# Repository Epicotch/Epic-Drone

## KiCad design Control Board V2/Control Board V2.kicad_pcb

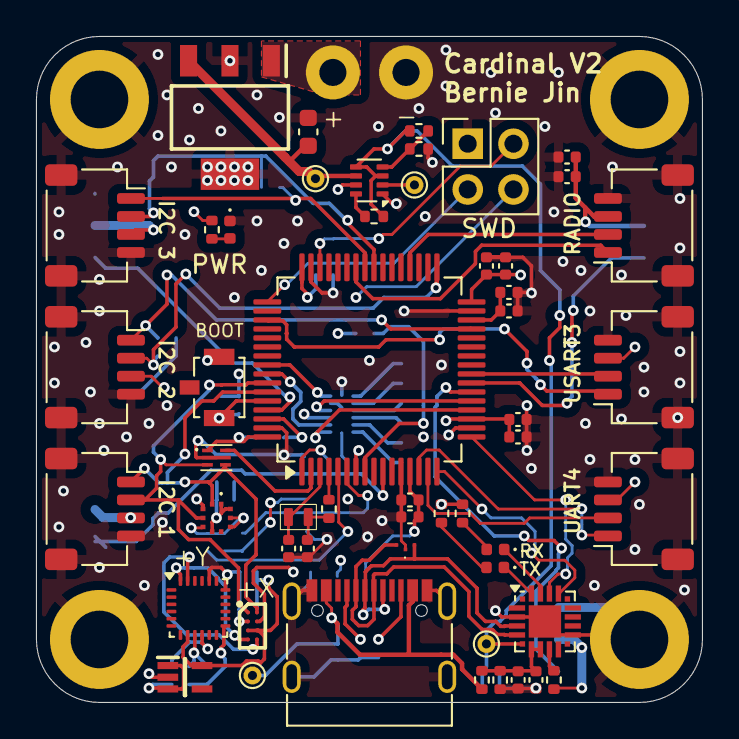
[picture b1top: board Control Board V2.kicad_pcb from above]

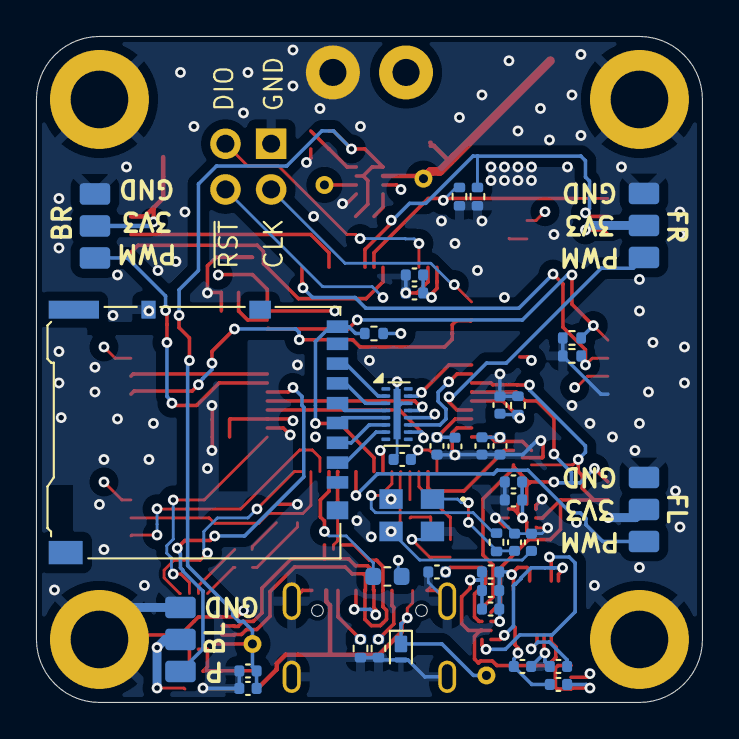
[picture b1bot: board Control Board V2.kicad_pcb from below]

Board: 4 copper layers, 37.0 x 37.0 mm, 96 parts (39 on the bottom side), 67 nets.

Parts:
BT1: 6S LIPO; Castellated_Power
C1, C2, C3, C6, C7, C8, C9, C29, C31, C33: 0.1uF; C_0402_1005Metric
C4, C5, C13, C19, C21, C23, C25, C26: 1uF; C_0402_1005Metric
C10, C34: 6pF; C_0402_1005Metric
C11, C12, C18, C20, C22, C24, C27: 100nF; C_0402_1005Metric
C14, C15, C16, C17: 2.2uF; C_0402_1005Metric
C28, C30: 4.7uF; C_0402_1005Metric
C32: 10uF; C_0603_1608Metric
C35, C36: 18pF; C_0402_1005Metric
D2: ESD122DMYR
D3, D7: 150040VS73240; LED_0402_1005Metric
D4: 150040RS73240; LED_0402_1005Metric
D5: PTVS5V0Z1USK; Nexperia_DSN1608-2_1.6x0.8mm
FB1: FCM1608KF-601T05; L_0603_1608Metric
H1, H2, H3, H4: MountingHole_Pad; MountingHole_3.2mm_M3_ISO14580_Pad
IC1: MIC5365-1.8YC5-TR; SOT65P210X110-5N
IC2: TCA9406YZPR; BGA8C50P2X4_89X189X50
IC3: BMP390
IC4: M24C02-FMH6TG; M24C32FMH6TG
IC5: MIC2920A-3.3WS-TR; SOT230P700X180-4N
J1: Conn_ARM_SWD_TagConnect_TC2030-NL; PinHeader_2x02_P2.54mm_Vertical
J2: Micro_SD_Card_Det1; microSD_HC_Hirose_DM3AT-SF-PEJM5
J30, J31, J32, J33: Conn_01x03_Pin; Breakout_Servo_Pad
J34: I2C_1; JST_SH_SM04B-SRSS-TB_1x04-1MP_P1.00mm_Horizontal
J35: USB_C_Receptacle_USB2.0_16P; USB_C_Receptacle_G-Switch_GT-USB-7010ASV
J36: I2C_2; JST_SH_SM04B-SRSS-TB_1x04-1MP_P1.00mm_Horizontal
J37: I2C_3; JST_SH_SM04B-SRSS-TB_1x04-1MP_P1.00mm_Horizontal
J38: UART4; JST_SH_SM04B-SRSS-TB_1x04-1MP_P1.00mm_Horizontal
J39: USART3; JST_SH_SM04B-SRSS-TB_1x04-1MP_P1.00mm_Horizontal
J40: RADIO; JST_SH_SM04B-SRSS-TB_1x04-1MP_P1.00mm_Horizontal
R1: 820k; R_0402_1005Metric
R2: 1.1k; R_0402_1005Metric
R7, R15, R18, R19, R20, R21, R22: 10k; R_0402_1005Metric
R8, R9: 5.1k; R_0402_1005Metric
R10: 1k; R_0402_1005Metric
R11: 22.1k; R_0402_1005Metric
R12: 47.5k; R_0402_1005Metric
R13, R14, R23: 82; R_0402_1005Metric
R16: 4.7k; R_0402_1005Metric
R17: 22k; R_0402_1005Metric
SW2: B3U-1100P; SW_SPST_B3U-1100P
TP1, TP2, TP3, TP4: TestPoint; TestPoint_THTPad_D1.0mm_Drill0.5mm
U1: ICM-20948; InvenSense_QFN-24_3x3mm_P0.4mm
U2: STM32H562RITx; LQFP-64_10x10mm_P0.5mm
U3: CP2102N-Axx-xQFN20; SiliconLabs_QFN-20-1EP_3x3mm_P0.5mm_EP1.8x1.8mm
U5: TPD8F003; WSON-16_3.3x1.35_P0.4mm
U6: TPS2116DRL; SOT-583-8
Y1: ECS-.327-6-16-TR3
Y2: ECS-80-12-33-JGN-TR; ECS801233JGNTR

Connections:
+1V8: C2.2, C5.2, C7.2, IC1.5 (VOUT), IC2.C1 (VCCA), IC2.C2 (OE), U1.8 (VDDIO)
+3V3: C1.1, C4.1, C6.2, C8.1, C9.1, C11.2, C18.1, C19.1, C20.1, C21.1, C22.1, C23.1, C24.1, C25.1, C26.2, C27.2, FB1.1, IC1.2 (GND), IC2.B2 (VCCB), IC3.1 (VDDIO), IC3.6 (CSB), IC3.10 (VDD), IC4.1 (VCC), J30.2, J31.2, J32.2, J33.2, J34.3, J36.3, J37.3, J38.3, J39.3, J40.3, R7.2, R10.1, R23.2, SW2.1, TP2.1, U1.13 (VDD), U2.1 (VBAT), U2.19 (VDD), U2.32 (VDD), U2.48 (VDD), U2.64 (VDD), U5.12 (Ch5_Out), U6.2 (VOUT), U6.7 (VOUT)
+3V3USB: C30.1, C31.1, R15.1, R16.1, TP3.1, U3.6 (VDD), U6.3 (VIN1), U6.5 (MODE)
+VBAT: C32.2, IC5.3 (OUTPUT), TP1.1, U6.6 (VIN2)
+VBUS: D5.1 (K), J35.A4 (VBUS), J35.A9 (VBUS), J35.B4 (VBUS), J35.B9 (VBUS), R11.1, TP4.1
/BL_PWM: J31.1, U2.22 (PA6)
/BR_PWM: J33.1, U2.23 (PA7)
/FL_PWM: J30.1, U2.10 (PC2)
/FR_PWM: J32.1, U2.61 (PB8)
/HSE_IN: C36.1, U2.5 (PH0), Y2.3 (OUT/IN)
/HSE_OUT: R2.2, U2.6 (PH1)
/LSE_IN: C10.1, U2.3 (PC14), Y1.1
/LSE_OUT: R1.2, U2.4 (PC15)
/RADIO_RX: J40.1, U2.42 (PA9)
/RADIO_TX: J40.2, U2.36 (PB15)
/RESET: J1.3 (~RESET), U2.7 (NRST)
/SD_CS: U2.20 (PA4), U5.10 (Ch7_Out)
/SD_DET: J2.9 (DET), R7.1, U2.8 (PC0)
/SPI1_MISO: U2.56 (PB4(NJTRST)), U5.15 (Ch2_Out)
/SPI1_SCK: U2.21 (PA5), U5.13 (Ch4_Out)
/SPI2_MOSI: U2.57 (PB5), U5.11 (Ch6_Out)
/SWCLK: J1.4 (SWCLK), U2.49 (PA14(JTCK)
/SWDIO: J1.2 (SWDIO), U2.46 (PA13(JTMS)
/USART2_RX: U2.17 (PA3), U3.18 (TXD)
/USART2_TX: U2.16 (PA2), U3.17 (RXD)
/USB to UART/D+: D2.2 (IO1), J35.A6 (D+), J35.B6 (D+), U3.4 (D+)
/USB to UART/D-: D2.3 (IO2), J35.A7 (D-), J35.B7 (D-), U3.5 (D-)
/USB to UART/VBUS: C28.1, C29.1, R11.2, R12.1, U3.7 (VREGIN), U3.8 (VBUS)
/~WC: IC4.5 (~WC), U2.2 (PC13)
GND: BT1.2 (-), C1.2, C2.1, C3.1, C5.1, C6.1, C7.1, C8.2, C9.2, C10.2, C11.1, C12.2, C13.2, C14.1, C15.1, C16.1, C17.1, C18.2, C19.2, C20.2, C21.2, C22.2, C23.2, C24.2, C25.2, C26.1, C27.1, C28.2, C29.2, C30.2, C31.2, C32.1, C33.2, C34.2, C35.2, C36.2, D2.1 (GROUND), D5.2 (A), D7.1 (K), H1.1, H2.1, H3.1, H4.1, IC2.B1 (GND), IC3.3 (VSS_1), IC3.5 (SDO), IC3.8 (VSS_2), IC3.9 (VSS_3), IC4.2 (VSS), IC5.2 (GROUND), IC5.4 (TAB), J1.5 (GND), J2.10 (SHIELD), J30.3, J31.3, J32.3, J33.3, J34.4, J34.MP (MountPin), J35.A1 (GND), J35.A12 (GND), J35.B1 (GND), J35.B12 (GND), J35.S1 (SHIELD), J36.4, J36.MP (MountPin), J37.4, J37.MP (MountPin), J38.4, J38.MP (MountPin), J39.4, J39.MP (MountPin), J40.4, J40.MP (MountPin), R8.2, R9.2, R12.2, R13.2, R14.2, R17.2, R18.2, R19.2, R20.2, R21.2, R22.2, U1.9 (SDO/AD0), U1.18 (GND), U1.20 (GND), U2.12 (VSSA), U2.18 (VSS), U2.31 (VSS), U2.47 (VSS), U2.63 (VSS), U3.3 (GND), U3.12 (GND), U3.21 (GND), U5.14 (Ch3_Out), U5.17 (GND), U6.1 (GND), Y2.2 (GND_1), Y2.4 (GND_2)
I2C_1_SCL: IC2.A2 (SCL_B), IC3.2 (SCK), IC4.4 (SCL), J34.1, U2.59 (PB7)
I2C_1_SDA: IC2.A1 (SDA_B), IC3.4 (SDI), IC4.3 (SDA), J34.2, U2.58 (PB6)
I2C_2_SCL: J36.1, R18.1, U2.29 (PB10)
I2C_2_SDA: J36.2, R19.1, U2.33 (PB12)
I2C_3_SCL: J37.1, R20.1, U2.41 (PA8)
I2C_3_SDA: J37.2, R21.1, U2.40 (PC9)
unnamed: BT1.1 (+), IC5.1 (INPUT)
unnamed: C14.2, C15.2, U2.30 (VCAP)
unnamed: C16.2, C17.2, U2.62 (VCAP)
unnamed: C34.1, R1.1, Y1.2
unnamed: D3.2 (A), R13.1
unnamed: D3.1 (K), U3.20 (~TXT/GPIO.2)
unnamed: D4.2 (A), R14.1
unnamed: D4.1 (K), U3.19 (~RXT/GPIO.3)
unnamed: D7.2 (A), R23.1
unnamed: C4.2, IC1.1 (VIN), IC1.3 (EN)
unnamed: IC2.D2 (SCL_A), U1.23 (SCL/SCLK)
unnamed: IC2.D1 (SDA_A), U1.24 (SDA/SDI)
unnamed: J2.5 (CLK), U5.4 (Ch4_In)
unnamed: J2.3 (CMD), U5.6 (Ch6_In)
unnamed: J2.7 (DAT0), U5.2 (Ch2_In)
unnamed: J2.2 (DAT3/CD), U5.7 (Ch7_In)
unnamed: J2.4 (VDD), U5.5 (Ch5_In)
unnamed: J2.6 (VSS), U5.3 (Ch3_In)
unnamed: J35.A5 (CC1), R8.1
unnamed: J35.B5 (CC2), R9.1
unnamed: C3.2, U1.10 (REGOUT)
unnamed: C33.1, R22.1, SW2.2, U2.60 (BOOT0)
unnamed: C12.1, C13.1, FB1.2, U2.13 (VDDA)
unnamed: R10.2, U3.9 (~RST)
unnamed: R16.2, R17.1, U6.4 (PR1)
unnamed: R15.2, U6.8 (ST)
unnamed: C35.1, R2.1, Y2.1 (IN/OUT)
UART4_RX: J38.2, U2.15 (PA1)
UART4_TX: J38.1, U2.14 (PA0)
USART3_RX: J39.2, U2.24 (PC4)
USART3_TX: J39.1, U2.51 (PC10)

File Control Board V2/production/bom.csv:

Designator,Footprint,Quantity,Value,LCSC Part #
BT1,Castellated_Power,1,6S LIPO,
"C1, C2, C29, C3, C31, C33, C6, C7, C8, C9",0402,10,0.1uF,
"C10, C34",0402,2,6pF,
"C11, C12, C18, C20, C22, C24, C27",0402,7,100nF,
"C13, C19, C21, C23, C25, C26, C4, C5",0402,8,1uF,
"C14, C15, C16, C17",0402,4,2.2uF,
"C28, C30",0402,2,4.7uF,
C32,0603,1,10uF,
"C35, C36",0402,2,18pF,
D2,ESD122DMYR,1,ESD122DMYR,
"D3, D7",0402,2,150040VS73240,
D4,0402,1,150040RS73240,
D5,Nexperia_DSN1608-2_1.6x0.8mm,1,PTVS5V0Z1USK,
FB1,0603,1,FCM1608KF-601T05,
IC1,SOT65P210X110-5N,1,MIC5365-1.8YC5-TR,
IC2,BGA8C50P2X4_89X189X50,1,TCA9406YZPR,
IC3,BMP390,1,BMP390,
IC4,M24C32FMH6TG,1,M24C02-FMH6TG,
IC5,SOT230P700X180-4N,1,MIC2920A-3.3WS-TR,
J2,microSD_HC_Hirose_DM3AT-SF-PEJM5,1,Micro_SD_Card_Det1,
"J30, J31, J32, J33",Breakout_Servo_Pad,4,Conn_01x03_Pin,
J34,JST_SH_SM04B-SRSS-TB_1x04-1MP_P1.00mm_Horizontal,1,I2C_1,
J35,USB_C_Receptacle_G-Switch_GT-USB-7010ASV,1,USB_C_Receptacle_USB2.0_16P,
J36,JST_SH_SM04B-SRSS-TB_1x04-1MP_P1.00mm_Horizontal,1,I2C_2,
J37,JST_SH_SM04B-SRSS-TB_1x04-1MP_P1.00mm_Horizontal,1,I2C_3,
J38,JST_SH_SM04B-SRSS-TB_1x04-1MP_P1.00mm_Horizontal,1,UART4,
J39,JST_SH_SM04B-SRSS-TB_1x04-1MP_P1.00mm_Horizontal,1,USART3,
J40,JST_SH_SM04B-SRSS-TB_1x04-1MP_P1.00mm_Horizontal,1,RADIO,
R1,0402,1,820k,
R10,0402,1,1k,
R11,0402,1,22.1k,
R12,0402,1,47.5k,
"R13, R14, R23",0402,3,82,
"R15, R18, R19, R20, R21, R22, R7",0402,7,10k,
R16,0402,1,4.7k,
R17,0402,1,22k,
R2,0402,1,1.1k,
"R8, R9",0402,2,5.1k,
SW2,SW_SPST_B3U-1100P,1,B3U-1100P,
"TP1, TP2, TP3, TP4",TestPoint_THTPad_D1.0mm_Drill0.5mm,4,TestPoint,
U1,InvenSense_QFN-24_3x3mm_P0.4mm,1,ICM-20948,
U2,LQFP-64_10x10mm_P0.5mm,1,STM32H562RITx,
U3,SiliconLabs_QFN-20-1EP_3x3mm_P0.5mm_EP1.8x1.8mm,1,CP2102N-Axx-xQFN20,
U5,WSON-16_3.3x1.35_P0.4mm,1,TPD8F003,
U6,SOT-583-8,1,TPS2116DRL,
Y1,ECS-.327-6-16-TR3,1,ECS-.327-6-16-TR3,
Y2,ECS801233JGNTR,1,ECS-80-12-33-JGN-TR,

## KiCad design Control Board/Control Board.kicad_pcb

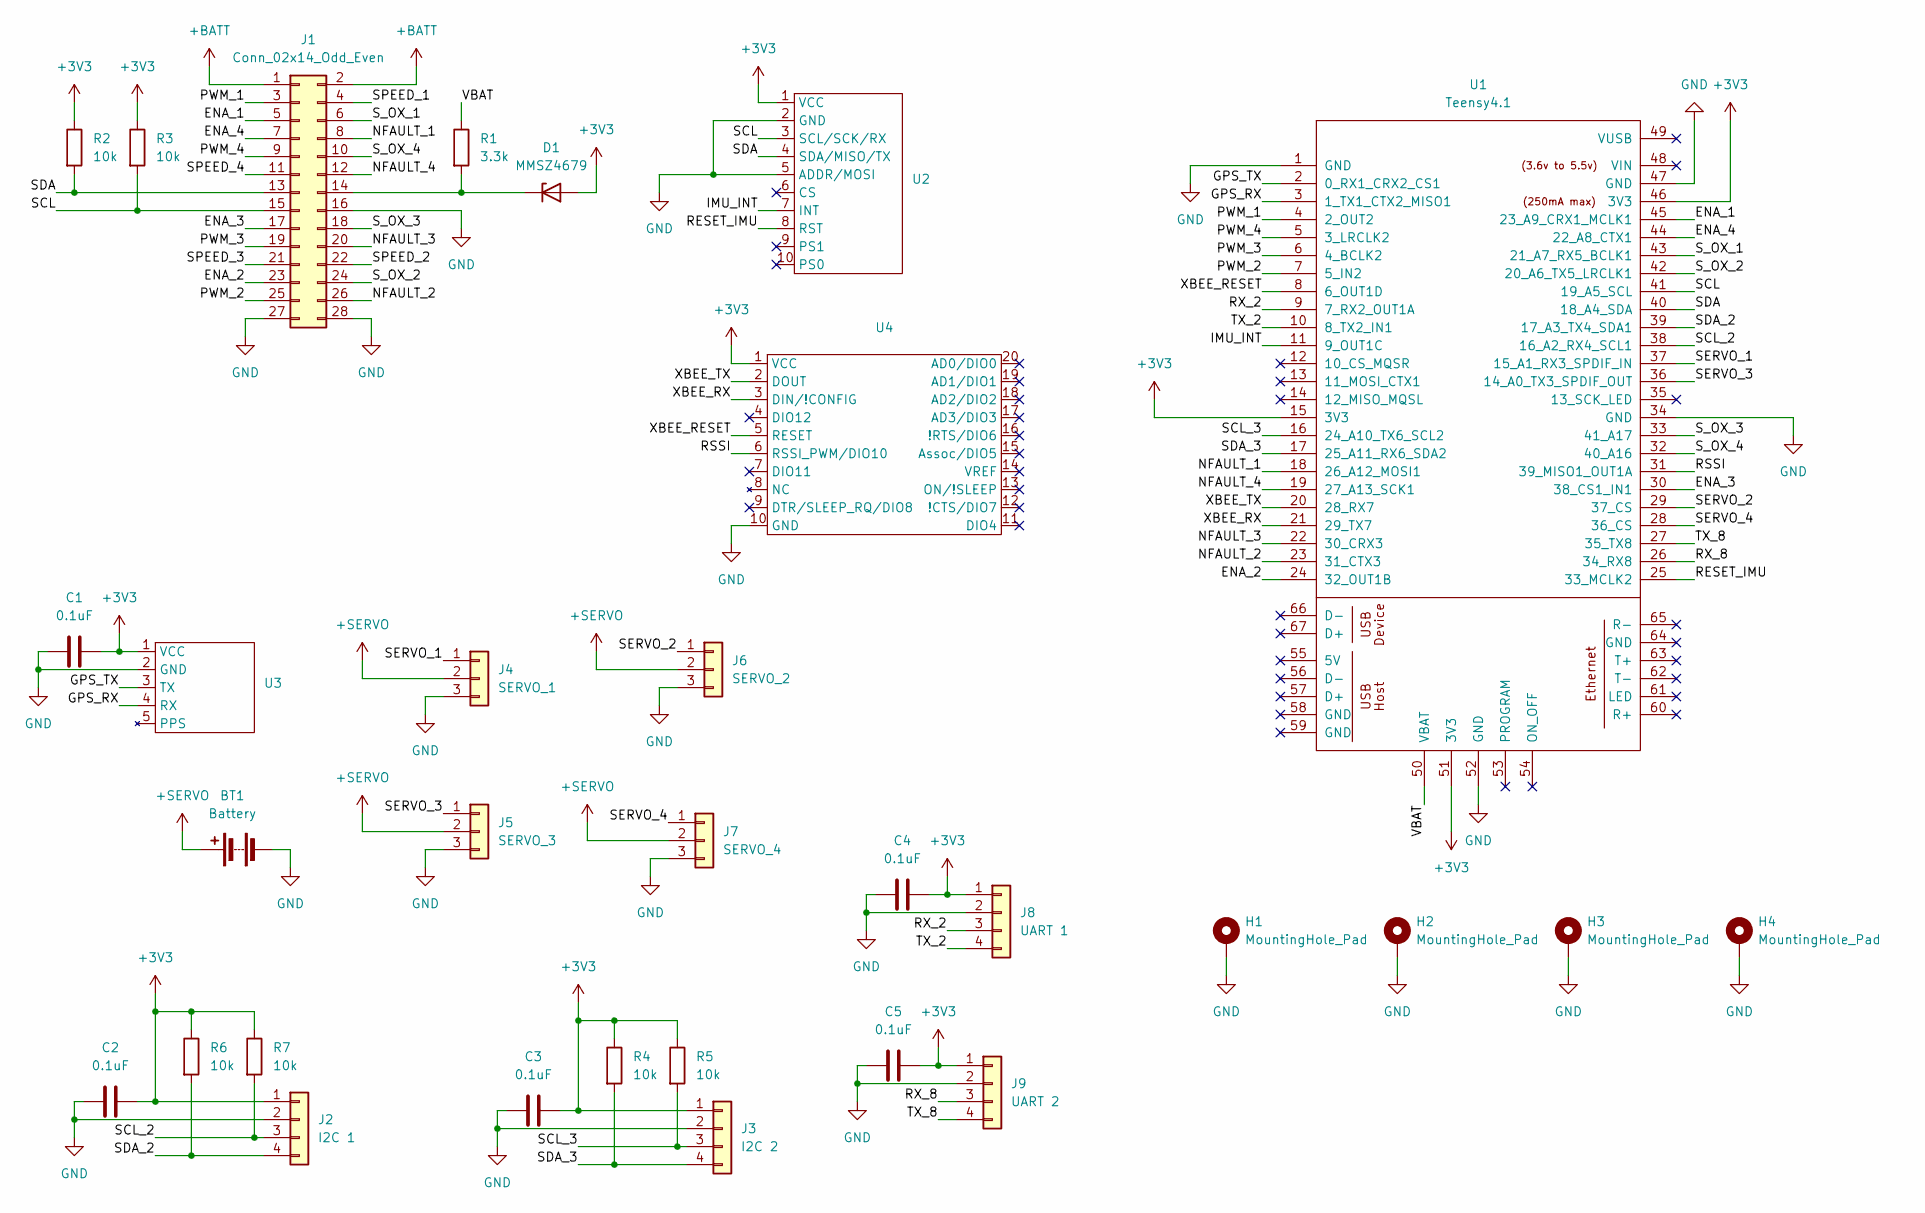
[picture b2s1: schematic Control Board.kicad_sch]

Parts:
BT1: Battery; AMASS_XT30PW-M_1x02_P2.50mm_Horizontal
C1, C2, C3, C4, C5: 0.1uF; C_0402_1005Metric
D1: MMSZ4679; D_SOD-123
H1, H2, H3, H4: MountingHole_Pad; MountingHole_3.2mm_M3_Pad
J1: Conn_02x14_Odd_Even; PinHeader_2x14_P2.54mm_Vertical
J2: I2C 1; PinHeader_1x04_P2.54mm_Vertical
J3: I2C 2; PinHeader_1x04_P2.54mm_Vertical
J4: SERVO_1; PinHeader_1x03_P2.54mm_Horizontal
J5: SERVO_3; PinHeader_1x03_P2.54mm_Horizontal
J6: SERVO_2; PinHeader_1x03_P2.54mm_Horizontal
J7: SERVO_4; PinHeader_1x03_P2.54mm_Horizontal
J8: UART 1; PinHeader_1x04_P2.54mm_Vertical
J9: UART 2; PinHeader_1x04_P2.54mm_Vertical
R1: 3.3k; R_0402_1005Metric
R2, R3, R4, R5, R6, R7: 10k; R_0402_1005Metric
U1: Teensy4.1; Teensy41
U2: BNO055_PCB
U3: ATGM336H_PCB
U4: XBEE_RR_THT

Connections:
+3V3: C1.2, C2.2, C3.2, C4.2, C5.2, D1.2 (A), J2.1, J3.1, J8.1, J9.1, R2.1, R3.1, R4.1, R5.1, R6.1, R7.1, U1.15 (3V3), U1.46 (3V3), U1.51 (3V3), U2.1 (VCC), U3.1 (VCC), U4.1 (VCC)
+BATT: J1.1, J1.2
+SERVO: BT1.1 (+), J4.2, J5.2, J6.2, J7.2
/ENA_1: J1.5, U1.45 (23_A9_CRX1_MCLK1)
/ENA_2: J1.23, U1.24 (32_OUT1B)
/ENA_3: J1.17, U1.30 (38_CS1_IN1)
/ENA_4: J1.7, U1.44 (22_A8_CTX1)
/GPS_RX: U1.3 (1_TX1_CTX2_MISO1), U3.4 (RX)
/GPS_TX: U1.2 (0_RX1_CRX2_CS1), U3.3 (TX)
/IMU_INT: U1.11 (9_OUT1C), U2.7 (INT)
/NFAULT_1: J1.8, U1.18 (26_A12_MOSI1)
/NFAULT_2: J1.26, U1.23 (31_CTX3)
/NFAULT_3: J1.20, U1.22 (30_CRX3)
/NFAULT_4: J1.12, U1.19 (27_A13_SCK1)
/PWM_1: J1.3, U1.4 (2_OUT2)
/PWM_2: J1.25, U1.7 (5_IN2)
/PWM_3: J1.19, U1.6 (4_BCLK2)
/PWM_4: J1.9, U1.5 (3_LRCLK2)
/RESET_IMU: U1.25 (33_MCLK2), U2.8 (RST)
/RSSI: U1.31 (39_MISO1_OUT1A), U4.6 (RSSI_PWM/DIO10)
/RX_2: J8.3, U1.9 (7_RX2_OUT1A)
/RX_8: J9.3, U1.26 (34_RX8)
/SCL: J1.15, R3.2, U1.41 (19_A5_SCL), U2.3 (SCL/SCK/RX)
/SCL_2: J2.3, R7.2, U1.38 (16_A2_RX4_SCL1)
/SCL_3: J3.3, R5.2, U1.16 (24_A10_TX6_SCL2)
/SDA: J1.13, R2.2, U1.40 (18_A4_SDA), U2.4 (SDA/MISO/TX)
/SDA_2: J2.4, R6.2, U1.39 (17_A3_TX4_SDA1)
/SDA_3: J3.4, R4.2, U1.17 (25_A11_RX6_SDA2)
/SERVO_1: J4.1, U1.37 (15_A1_RX3_SPDIF_IN)
/SERVO_2: J6.1, U1.29 (37_CS)
/SERVO_3: J5.1, U1.36 (14_A0_TX3_SPDIF_OUT)
/SERVO_4: J7.1, U1.28 (36_CS)
/SPEED_1: J1.4
/SPEED_2: J1.22
/SPEED_3: J1.21
/SPEED_4: J1.11
/S_OX_1: J1.6, U1.43 (21_A7_RX5_BCLK1)
/S_OX_2: J1.24, U1.42 (20_A6_TX5_LRCLK1)
/S_OX_3: J1.18, U1.33 (41_A17)
/S_OX_4: J1.10, U1.32 (40_A16)
/TX_2: J8.4, U1.10 (8_TX2_IN1)
/TX_8: J9.4, U1.27 (35_TX8)
/VBAT: R1.1, U1.50 (VBAT)
/XBEE_RESET: U1.8 (6_OUT1D), U4.5 (RESET)
/XBEE_RX: U1.21 (29_TX7), U4.3 (DIN/!CONFIG)
/XBEE_TX: U1.20 (28_RX7), U4.2 (DOUT)
GND: BT1.2 (-), C1.1, C2.1, C3.1, C4.1, C5.1, H1.1, H2.1, H3.1, H4.1, J1.16, J1.27, J1.28, J2.2, J3.2, J4.3, J5.3, J6.3, J7.3, J8.2, J9.2, U1.1 (GND), U1.34 (GND), U1.47 (GND), U1.52 (GND), U2.2 (GND), U2.5 (ADDR/MOSI), U3.2 (GND), U4.10 (GND)
unnamed: D1.1 (K), J1.14, R1.2

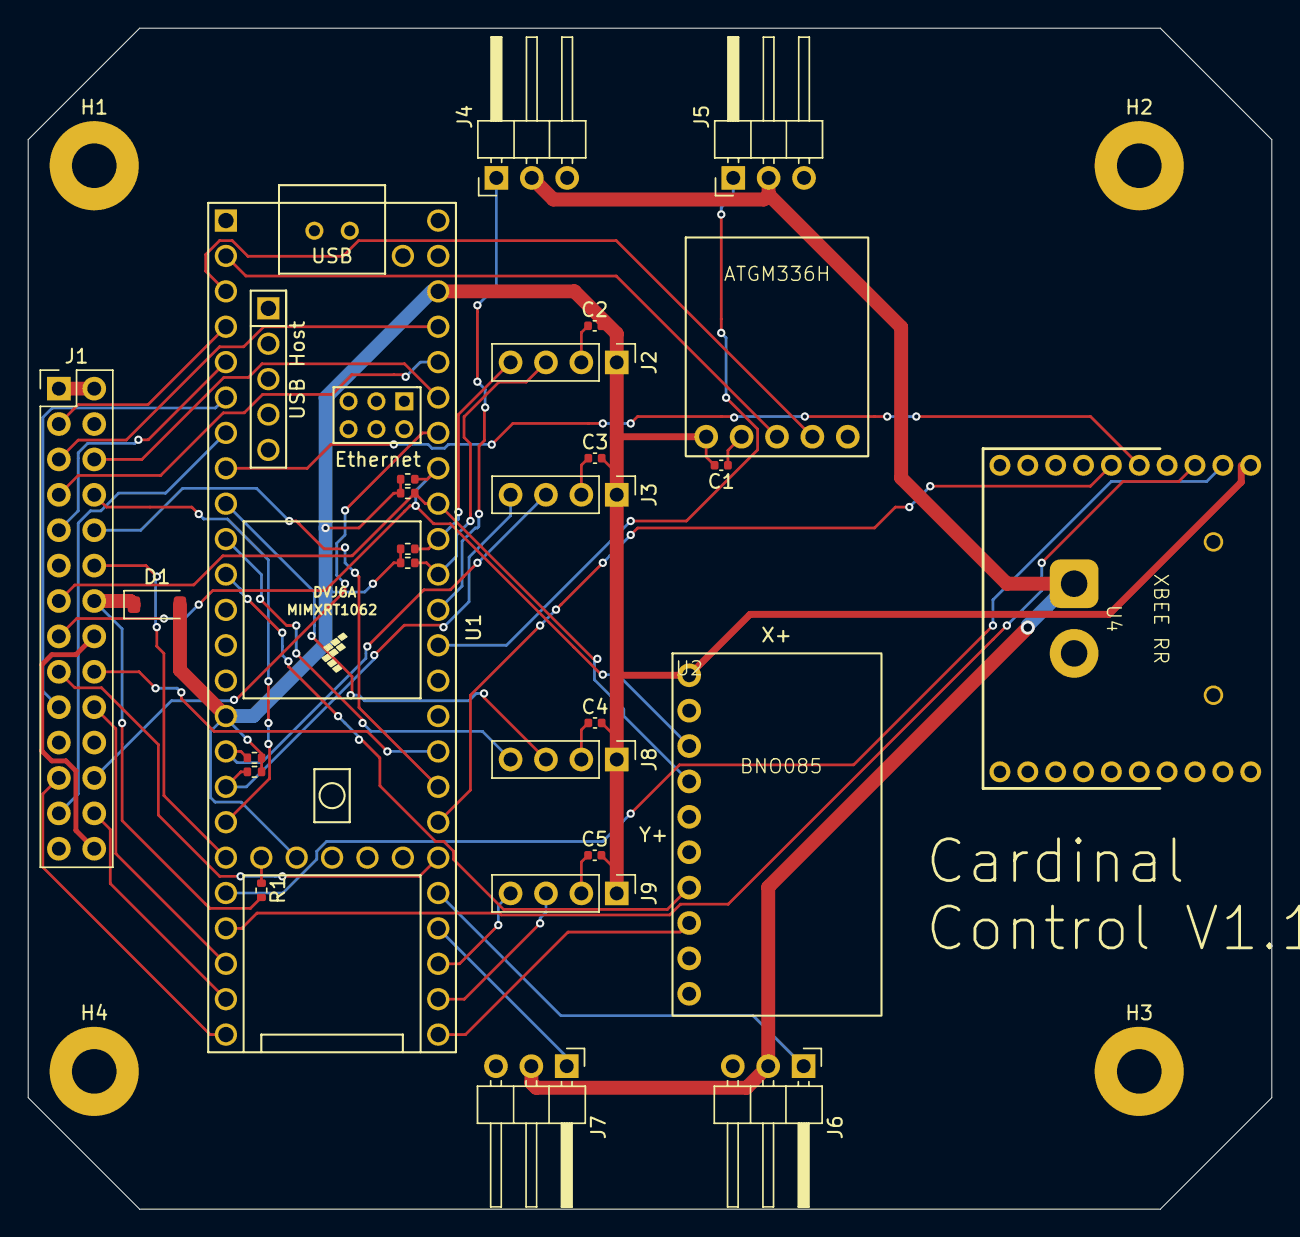
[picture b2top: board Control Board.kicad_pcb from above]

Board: 2 copper layers, 89.2 x 84.8 mm, 31 parts (1 on the bottom side), 44 nets.

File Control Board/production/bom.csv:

Designator,Footprint,Quantity,Value,LCSC Part #
BT1,AMASS_XT30PW-M_1x02_P2.50mm_Horizontal,1,Battery,
"C1, C2, C3, C4, C5",0402,5,0.1uF,
D1,D_SOD-123,1,MMSZ4679,
J2,PinHeader_1x04_P2.54mm_Vertical,1,I2C 1,
J3,PinHeader_1x04_P2.54mm_Vertical,1,I2C 2,
J4,PinHeader_1x03_P2.54mm_Horizontal,1,SERVO_1,
J5,PinHeader_1x03_P2.54mm_Horizontal,1,SERVO_3,
J6,PinHeader_1x03_P2.54mm_Horizontal,1,SERVO_2,
J7,PinHeader_1x03_P2.54mm_Horizontal,1,SERVO_4,
J8,PinHeader_1x04_P2.54mm_Vertical,1,UART 1,
J9,PinHeader_1x04_P2.54mm_Vertical,1,UART 2,
R1,0402,1,3.3k,
"R2, R3, R4, R5, R6, R7",0402,6,4.7k,

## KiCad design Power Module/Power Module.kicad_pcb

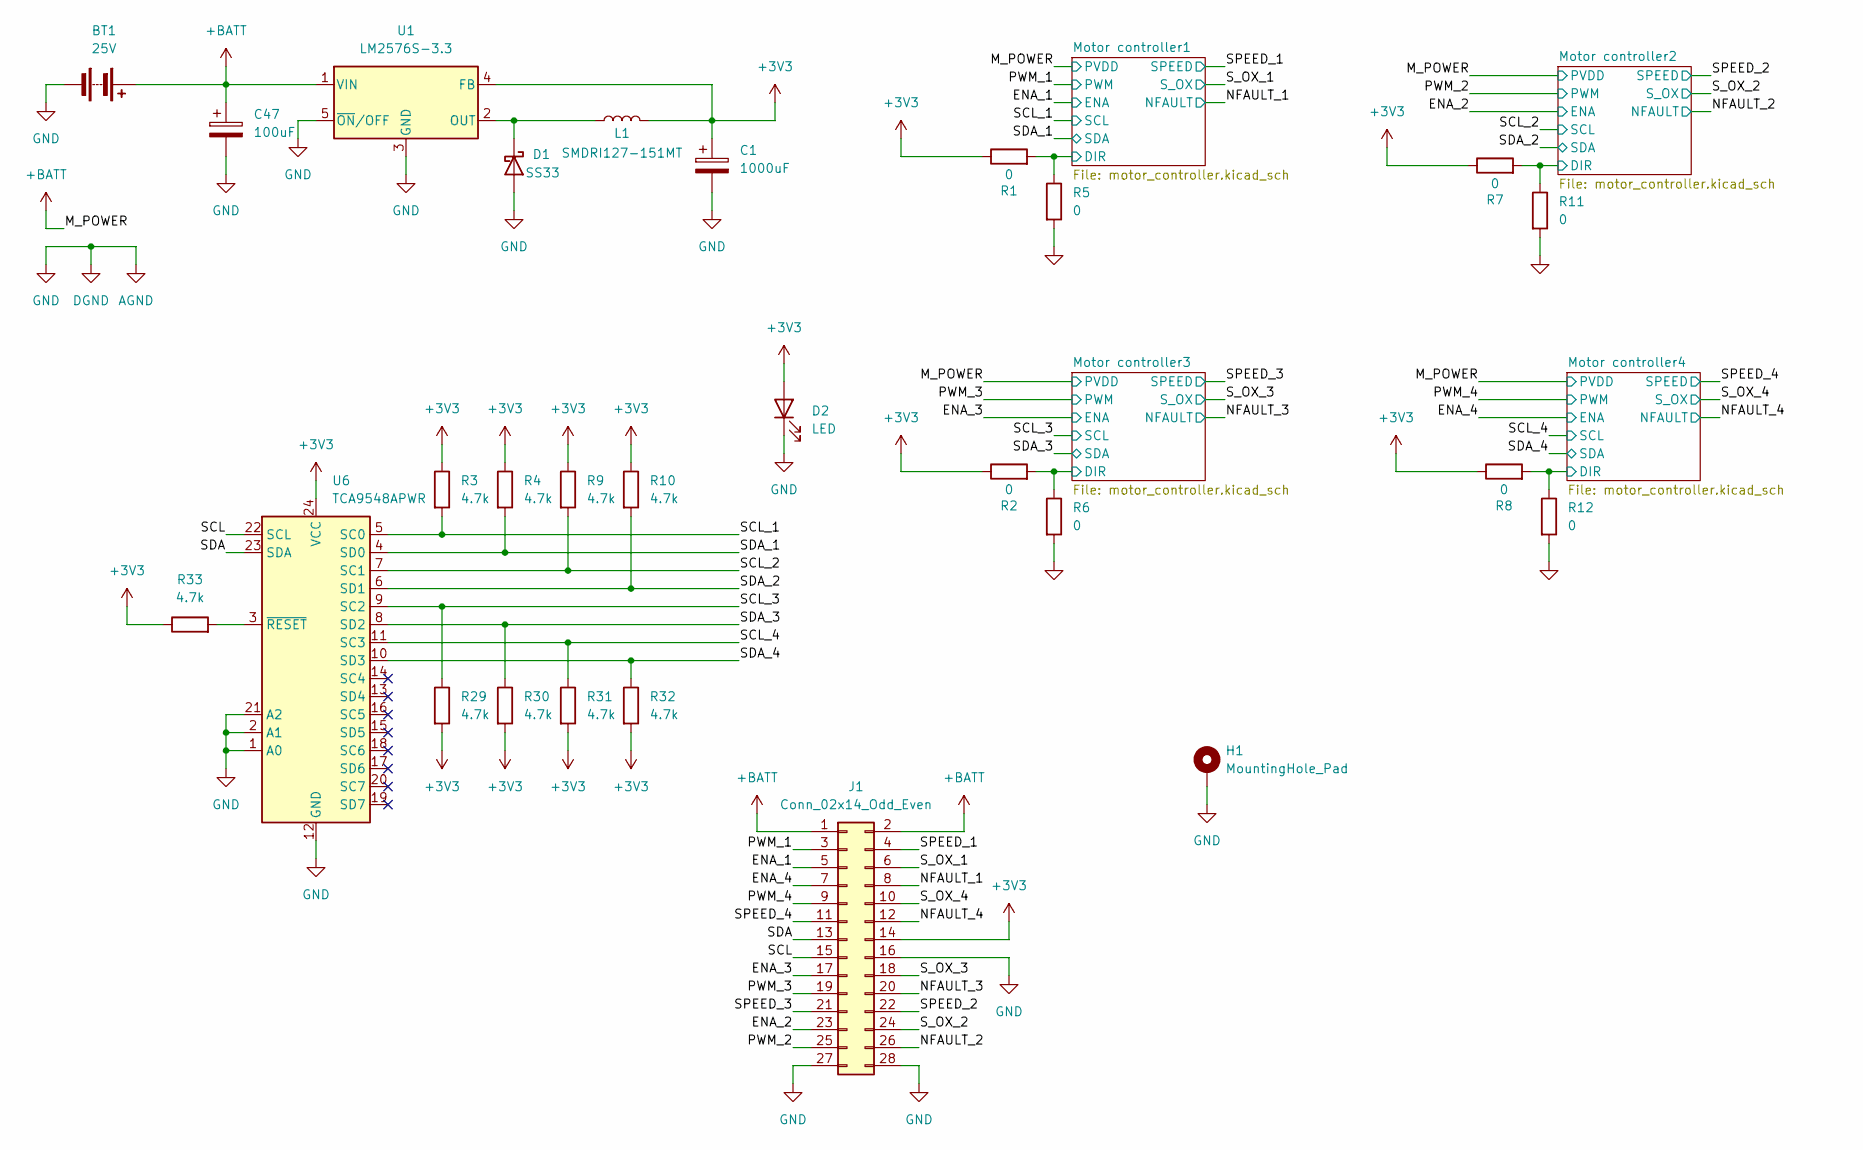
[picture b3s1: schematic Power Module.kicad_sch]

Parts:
BT1: 25V; AMASS_XT60PW-M_1x02_P7.20mm_Horizontal
C1: 1000uF; CP_EIA-7343-30_AVX-N
C47: 100uF; CP_EIA-7343-43_Kemet-X
D1: SS33; D_SMA
D2: LED; LED_0603_1608Metric
H1: MountingHole_Pad; MountingHole_3.2mm_M3_Pad
J1: Conn_02x14_Odd_Even; PinHeader_2x14_P2.54mm_Vertical
L1: SMDRI127-151MT; L_12x12mm_H6mm
R1, R2, R5, R6, R7, R8, R11, R12: 0; R_0603_1608Metric_Pad0.98x0.95mm_HandSolder
R3, R4, R9, R10, R29, R30, R31, R32, R33: 4.7k; R_0402_1005Metric
U1: LM2576S-3.3; TO-263-5_TabPin3
U6: TCA9548APWR; TSSOP-24_4.4x7.8mm_P0.65mm

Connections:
+3V3: C1.1, D2.2 (A), J1.14, L1.2, R1.1, R2.1, R3.1, R4.1, R7.1, R8.1, R9.1, R10.1, R29.2, R30.2, R31.2, R32.2, R33.1, U1.4 (FB), U6.24 (VCC); also elsewhere on the board
+BATT: BT1.1 (+), C47.1, J1.1, J1.2, U1.1 (VIN); also elsewhere on the board
/ENA_1: J1.5; also elsewhere on the board
/ENA_2: J1.23; also elsewhere on the board
/ENA_3: J1.17; also elsewhere on the board
/ENA_4: J1.7; also elsewhere on the board
/Motor controller1/DIR: R1.2, R5.1; also elsewhere on the board
/Motor controller2/DIR: R7.2, R11.1; also elsewhere on the board
/Motor controller3/DIR: R2.2, R6.1; also elsewhere on the board
/Motor controller4/DIR: R8.2, R12.1; also elsewhere on the board
/NFAULT_1: J1.8; also elsewhere on the board
/NFAULT_2: J1.26; also elsewhere on the board
/NFAULT_3: J1.20; also elsewhere on the board
/NFAULT_4: J1.12; also elsewhere on the board
/PWM_1: J1.3; also elsewhere on the board
/PWM_2: J1.25; also elsewhere on the board
/PWM_3: J1.19; also elsewhere on the board
/PWM_4: J1.9; also elsewhere on the board
/SCL: J1.15, U6.22 (SCL)
/SCL_1: R3.2, U6.5 (SC0); also elsewhere on the board
/SCL_2: R9.2, U6.7 (SC1); also elsewhere on the board
/SCL_3: R29.1, U6.9 (SC2); also elsewhere on the board
/SCL_4: R31.1, U6.11 (SC3); also elsewhere on the board
/SDA: J1.13, U6.23 (SDA)
/SDA_1: R4.2, U6.4 (SD0); also elsewhere on the board
/SDA_2: R10.2, U6.6 (SD1); also elsewhere on the board
/SDA_3: R30.1, U6.8 (SD2); also elsewhere on the board
/SDA_4: R32.1, U6.10 (SD3); also elsewhere on the board
/SPEED_1: J1.4; also elsewhere on the board
/SPEED_2: J1.22; also elsewhere on the board
/SPEED_3: J1.21; also elsewhere on the board
/SPEED_4: J1.11; also elsewhere on the board
/S_OX_1: J1.6; also elsewhere on the board
/S_OX_2: J1.24; also elsewhere on the board
/S_OX_3: J1.18; also elsewhere on the board
/S_OX_4: J1.10; also elsewhere on the board
AGND: BT1.2 (-), C1.2, C47.2, D1.2 (A), D2.1 (K), H1.1, J1.16, J1.27, J1.28, R5.2, R6.2, R11.2, R12.2, U1.3 (GND), U1.5 (~ON/OFF), U6.1 (A0), U6.2 (A1), U6.12 (GND), U6.21 (A2); also elsewhere on the board
unnamed: D1.1 (K), L1.1, U1.2 (OUT)
unnamed: R33.2, U6.3 (~RESET)

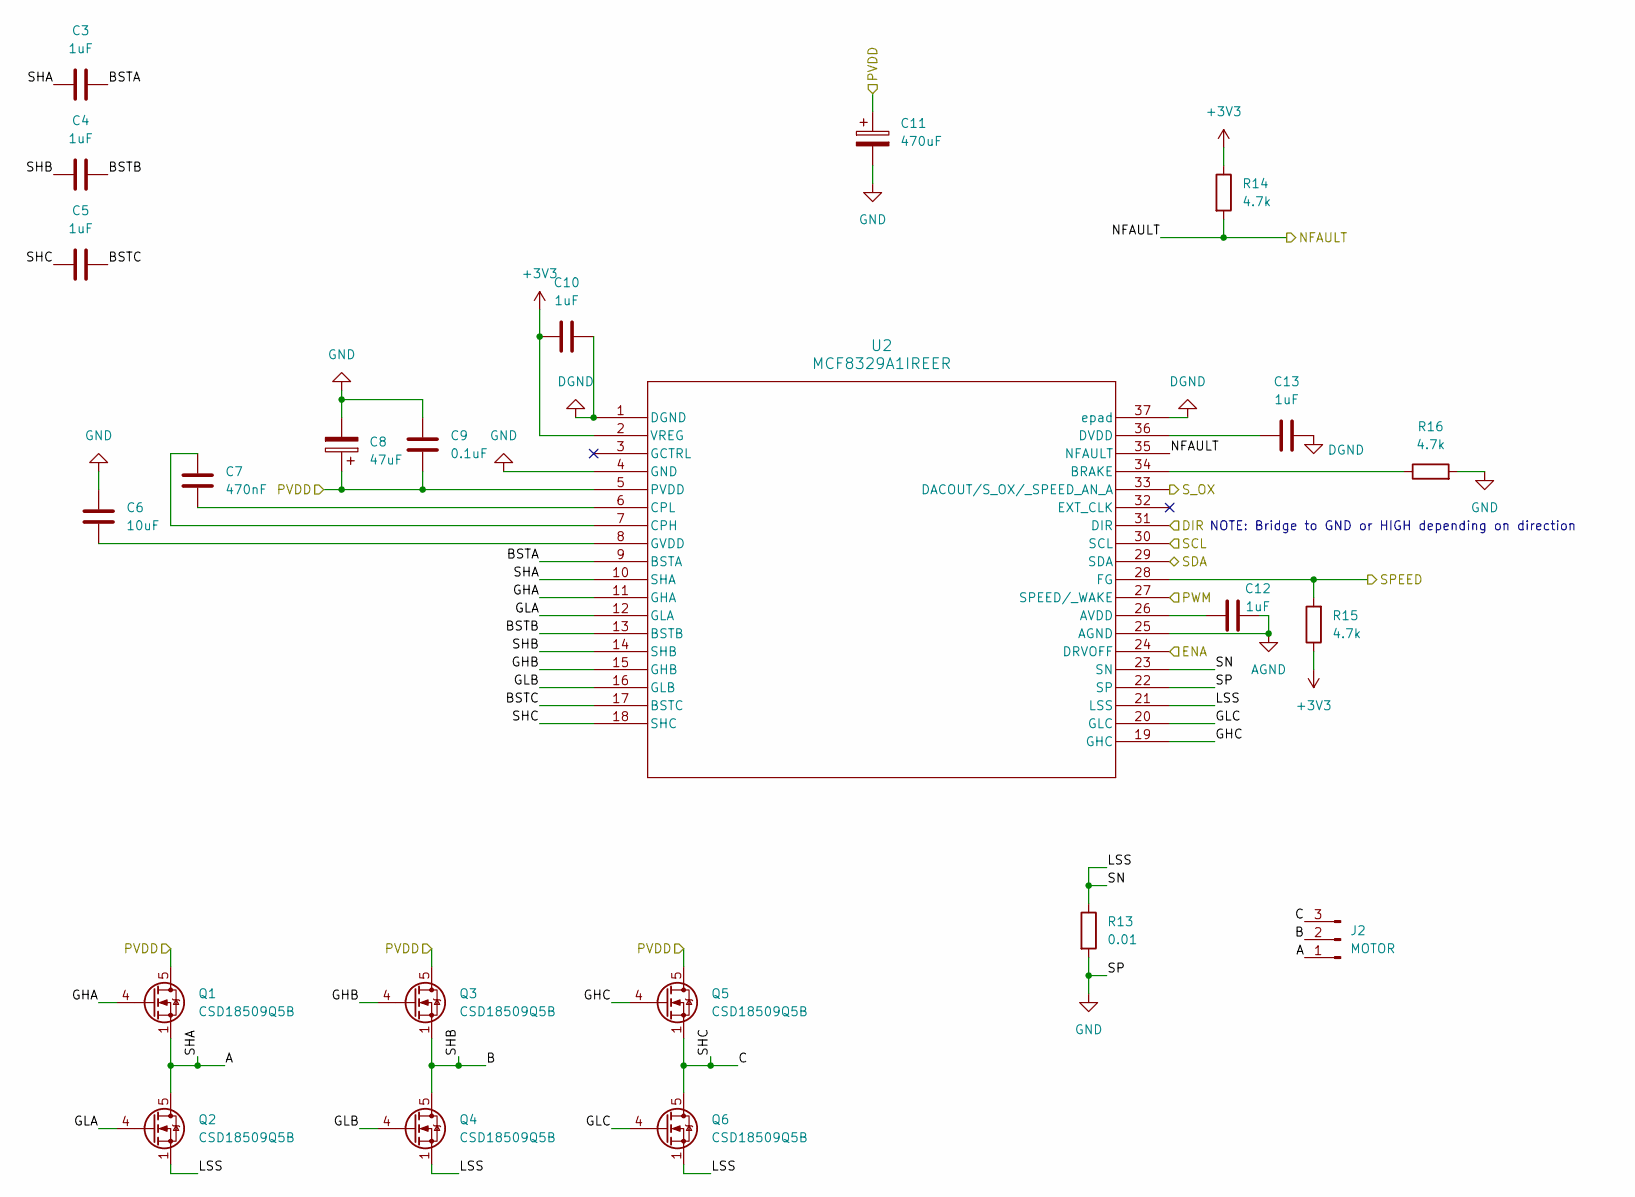
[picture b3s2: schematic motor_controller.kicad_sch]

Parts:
C3, C4, C5, C10, C12, C13: 1uF; C_0402_1005Metric
C6: 10uF; C_0603_1608Metric
C7: 470nF; C_0402_1005Metric
C8: 47uF; CP_Elec_6.3x7.7
C9: 0.1uF; C_0603_1608Metric
C11: 470uF; CP_Elec_10x10.5
J2: MOTOR; Edge_Solderpoint
Q1, Q2, Q3, Q4, Q5, Q6: CSD18509Q5B; TDSON-8-1
R13: 0.01; R_2512_6332Metric
R14, R15, R16: 4.7k; R_0402_1005Metric
U2: MCF8329A1IREER; WQFN36_REE_TEX

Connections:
+3V3: C10.1, R14.1, R15.1, U2.2 (VREG); also elsewhere on the board
+BATT: C8.1, C9.2, C11.1, Q1.5 (D), Q3.5 (D), Q5.5 (D), U2.5 (PVDD); also elsewhere on the board
/ENA_2: U2.24 (DRVOFF); also elsewhere on the board
/Motor controller2/A: C3.1, J2.1, Q1.1 (S), Q1.2 (S), Q1.3 (S), Q2.5 (D), U2.10 (SHA)
/Motor controller2/B: C4.1, J2.2, Q3.1 (S), Q3.2 (S), Q3.3 (S), Q4.5 (D), U2.14 (SHB)
/Motor controller2/BSTA: C3.2, U2.9 (BSTA)
/Motor controller2/BSTB: C4.2, U2.13 (BSTB)
/Motor controller2/BSTC: C5.2, U2.17 (BSTC)
/Motor controller2/C: C5.1, J2.3, Q5.1 (S), Q5.2 (S), Q5.3 (S), Q6.5 (D), U2.18 (SHC)
/Motor controller2/DIR: U2.31 (DIR); also elsewhere on the board
/Motor controller2/GHA: Q1.4 (G), U2.11 (GHA)
/Motor controller2/GHB: Q3.4 (G), U2.15 (GHB)
/Motor controller2/GHC: Q5.4 (G), U2.19 (GHC)
/Motor controller2/GLA: Q2.4 (G), U2.12 (GLA)
/Motor controller2/GLB: Q4.4 (G), U2.16 (GLB)
/Motor controller2/GLC: Q6.4 (G), U2.20 (GLC)
/Motor controller2/LSS: Q2.1 (S), Q2.2 (S), Q2.3 (S), Q4.1 (S), Q4.2 (S), Q4.3 (S), Q6.1 (S), Q6.2 (S), Q6.3 (S), R13.1, U2.21 (LSS), U2.23 (SN)
/NFAULT_2: R14.2, U2.35 (NFAULT); also elsewhere on the board
/PWM_2: U2.27 (SPEED/_WAKE); also elsewhere on the board
/SCL_2: U2.30 (SCL); also elsewhere on the board
/SDA_2: U2.29 (SDA); also elsewhere on the board
/SPEED_2: R15.2, U2.28 (FG); also elsewhere on the board
/S_OX_2: U2.33 (DACOUT/S_OX/_SPEED_AN_A); also elsewhere on the board
AGND: C6.1, C8.2, C9.1, C10.2, C11.2, C12.2, C13.2, R13.2, R16.2, U2.1 (DGND), U2.4 (GND), U2.22 (SP), U2.25 (AGND), U2.37 (epad); also elsewhere on the board
unnamed: C12.1, U2.26 (AVDD)
unnamed: R16.1, U2.34 (BRAKE)
unnamed: C7.1, U2.7 (CPH)
unnamed: C7.2, U2.6 (CPL)
unnamed: C13.1, U2.36 (DVDD)
unnamed: C6.2, U2.8 (GVDD)

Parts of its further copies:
C14, C15, C16, C21, C23, C24, C25, C26, C27, C32, C34, C35, C36, C37, C38, C43, C45, C46: 1uF; C_0402_1005Metric
C17, C28, C39: 10uF; C_0603_1608Metric
C18, C29, C40: 470nF; C_0402_1005Metric
C19, C30, C41: 47uF; CP_Elec_6.3x7.7
C20, C31, C42: 0.1uF; C_0603_1608Metric
C22, C33, C44: 470uF; CP_Elec_10x10.5
J3, J4, J5: MOTOR; Edge_Solderpoint
Q7, Q8, Q9, Q10, Q11, Q12, Q13, Q14, Q15, Q16, Q17, Q18, Q19, Q20, Q21, Q22, Q23, Q24: CSD18509Q5B; TDSON-8-1
R17, R21, R25: 0.01; R_2512_6332Metric
R18, R19, R20, R22, R23, R24, R26, R27, R28: 4.7k; R_0402_1005Metric
U3, U4, U5: MCF8329A1IREER; WQFN36_REE_TEX

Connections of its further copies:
+3V3: C21.1, C32.1, C43.1, R18.1, R19.1, R22.1, R23.1, R26.1, R27.1, U3.2 (VREG), U4.2 (VREG), U5.2 (VREG); also elsewhere on the board
+BATT: C19.1, C20.2, C22.1, C30.1, C31.2, C33.1, C41.1, C42.2, C44.1, Q7.5 (D), Q9.5 (D), Q11.5 (D), Q13.5 (D), Q15.5 (D), Q17.5 (D), Q19.5 (D), Q21.5 (D), Q23.5 (D), U3.5 (PVDD), U4.5 (PVDD), U5.5 (PVDD); also elsewhere on the board
/ENA_1: U3.24 (DRVOFF); also elsewhere on the board
/ENA_3: U4.24 (DRVOFF); also elsewhere on the board
/ENA_4: U5.24 (DRVOFF); also elsewhere on the board
/Motor controller1/A: C14.1, J3.1, Q7.1 (S), Q7.2 (S), Q7.3 (S), Q8.5 (D), U3.10 (SHA)
/Motor controller1/B: C15.1, J3.2, Q9.1 (S), Q9.2 (S), Q9.3 (S), Q10.5 (D), U3.14 (SHB)
/Motor controller1/BSTA: C14.2, U3.9 (BSTA)
/Motor controller1/BSTB: C15.2, U3.13 (BSTB)
/Motor controller1/BSTC: C16.2, U3.17 (BSTC)
/Motor controller1/C: C16.1, J3.3, Q11.1 (S), Q11.2 (S), Q11.3 (S), Q12.5 (D), U3.18 (SHC)
/Motor controller1/DIR: U3.31 (DIR); also elsewhere on the board
/Motor controller1/GHA: Q7.4 (G), U3.11 (GHA)
/Motor controller1/GHB: Q9.4 (G), U3.15 (GHB)
/Motor controller1/GHC: Q11.4 (G), U3.19 (GHC)
/Motor controller1/GLA: Q8.4 (G), U3.12 (GLA)
/Motor controller1/GLB: Q10.4 (G), U3.16 (GLB)
/Motor controller1/GLC: Q12.4 (G), U3.20 (GLC)
/Motor controller1/LSS: Q8.1 (S), Q8.2 (S), Q8.3 (S), Q10.1 (S), Q10.2 (S), Q10.3 (S), Q12.1 (S), Q12.2 (S), Q12.3 (S), R17.1, U3.21 (LSS), U3.23 (SN)
/Motor controller3/A: C25.1, J4.1, Q13.1 (S), Q13.2 (S), Q13.3 (S), Q14.5 (D), U4.10 (SHA)
/Motor controller3/B: C26.1, J4.2, Q15.1 (S), Q15.2 (S), Q15.3 (S), Q16.5 (D), U4.14 (SHB)
/Motor controller3/BSTA: C25.2, U4.9 (BSTA)
/Motor controller3/BSTB: C26.2, U4.13 (BSTB)
/Motor controller3/BSTC: C27.2, U4.17 (BSTC)
/Motor controller3/C: C27.1, J4.3, Q17.1 (S), Q17.2 (S), Q17.3 (S), Q18.5 (D), U4.18 (SHC)
/Motor controller3/DIR: U4.31 (DIR); also elsewhere on the board
/Motor controller3/GHA: Q13.4 (G), U4.11 (GHA)
/Motor controller3/GHB: Q15.4 (G), U4.15 (GHB)
/Motor controller3/GHC: Q17.4 (G), U4.19 (GHC)
/Motor controller3/GLA: Q14.4 (G), U4.12 (GLA)
/Motor controller3/GLB: Q16.4 (G), U4.16 (GLB)
/Motor controller3/GLC: Q18.4 (G), U4.20 (GLC)
/Motor controller3/LSS: Q14.1 (S), Q14.2 (S), Q14.3 (S), Q16.1 (S), Q16.2 (S), Q16.3 (S), Q18.1 (S), Q18.2 (S), Q18.3 (S), R21.1, U4.21 (LSS), U4.23 (SN)
/Motor controller4/A: C36.1, J5.1, Q19.1 (S), Q19.2 (S), Q19.3 (S), Q20.5 (D), U5.10 (SHA)
/Motor controller4/B: C37.1, J5.2, Q21.1 (S), Q21.2 (S), Q21.3 (S), Q22.5 (D), U5.14 (SHB)
/Motor controller4/BSTA: C36.2, U5.9 (BSTA)
/Motor controller4/BSTB: C37.2, U5.13 (BSTB)
/Motor controller4/BSTC: C38.2, U5.17 (BSTC)
/Motor controller4/C: C38.1, J5.3, Q23.1 (S), Q23.2 (S), Q23.3 (S), Q24.5 (D), U5.18 (SHC)
/Motor controller4/DIR: U5.31 (DIR); also elsewhere on the board
/Motor controller4/GHA: Q19.4 (G), U5.11 (GHA)
/Motor controller4/GHB: Q21.4 (G), U5.15 (GHB)
/Motor controller4/GHC: Q23.4 (G), U5.19 (GHC)
/Motor controller4/GLA: Q20.4 (G), U5.12 (GLA)
/Motor controller4/GLB: Q22.4 (G), U5.16 (GLB)
/Motor controller4/GLC: Q24.4 (G), U5.20 (GLC)
/Motor controller4/LSS: Q20.1 (S), Q20.2 (S), Q20.3 (S), Q22.1 (S), Q22.2 (S), Q22.3 (S), Q24.1 (S), Q24.2 (S), Q24.3 (S), R25.1, U5.21 (LSS), U5.23 (SN)
/NFAULT_1: R18.2, U3.35 (NFAULT); also elsewhere on the board
/NFAULT_3: R22.2, U4.35 (NFAULT); also elsewhere on the board
/NFAULT_4: R26.2, U5.35 (NFAULT); also elsewhere on the board
/PWM_1: U3.27 (SPEED/_WAKE); also elsewhere on the board
/PWM_3: U4.27 (SPEED/_WAKE); also elsewhere on the board
/PWM_4: U5.27 (SPEED/_WAKE); also elsewhere on the board
/SCL_1: U3.30 (SCL); also elsewhere on the board
/SCL_3: U4.30 (SCL); also elsewhere on the board
/SCL_4: U5.30 (SCL); also elsewhere on the board
/SDA_1: U3.29 (SDA); also elsewhere on the board
/SDA_3: U4.29 (SDA); also elsewhere on the board
/SDA_4: U5.29 (SDA); also elsewhere on the board
/SPEED_1: R19.2, U3.28 (FG); also elsewhere on the board
/SPEED_3: R23.2, U4.28 (FG); also elsewhere on the board
/SPEED_4: R27.2, U5.28 (FG); also elsewhere on the board
/S_OX_1: U3.33 (DACOUT/S_OX/_SPEED_AN_A); also elsewhere on the board
/S_OX_3: U4.33 (DACOUT/S_OX/_SPEED_AN_A); also elsewhere on the board
/S_OX_4: U5.33 (DACOUT/S_OX/_SPEED_AN_A); also elsewhere on the board
AGND: C17.1, C19.2, C20.1, C21.2, C22.2, C23.2, C24.2, C28.1, C30.2, C31.1, C32.2, C33.2, C34.2, C35.2, C39.1, C41.2, C42.1, C43.2, C44.2, C45.2, C46.2, R17.2, R20.2, R21.2, R24.2, R25.2, R28.2, U3.1 (DGND), U3.4 (GND), U3.22 (SP), U3.25 (AGND), U3.37 (epad), U4.1 (DGND), U4.4 (GND), U4.22 (SP), U4.25 (AGND), U4.37 (epad), U5.1 (DGND), U5.4 (GND), U5.22 (SP), U5.25 (AGND), U5.37 (epad); also elsewhere on the board
unnamed: C23.1, U3.26 (AVDD)
unnamed: R20.1, U3.34 (BRAKE)
unnamed: C18.1, U3.7 (CPH)
unnamed: C18.2, U3.6 (CPL)
unnamed: C24.1, U3.36 (DVDD)
unnamed: C17.2, U3.8 (GVDD)
unnamed: C34.1, U4.26 (AVDD)
unnamed: R24.1, U4.34 (BRAKE)
unnamed: C29.1, U4.7 (CPH)
unnamed: C29.2, U4.6 (CPL)
unnamed: C35.1, U4.36 (DVDD)
unnamed: C28.2, U4.8 (GVDD)
unnamed: C45.1, U5.26 (AVDD)
unnamed: R28.1, U5.34 (BRAKE)
unnamed: C40.1, U5.7 (CPH)
unnamed: C40.2, U5.6 (CPL)
unnamed: C46.1, U5.36 (DVDD)
unnamed: C39.2, U5.8 (GVDD)

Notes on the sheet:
NOTE: Bridge to GND or HIGH depending on direction
